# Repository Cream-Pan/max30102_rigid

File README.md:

<div id="top"></div>

# MAX30102_rigid

MAX30102を用いた小型PPGセンサ用リジッド基板である．
耳装着型デバイスやウェアラブルデバイスへの組み込みを想定し，光電脈波（PPG）を取得するために設計した．

## 使用技術一覧

## 目次

1. [概要](#概要)
2. [基板仕様](#基板仕様)
3. [回路構成](#回路構成)
4. [ディレクトリ構成](#ディレクトリ構成)
5. [Git管理方針](#git管理方針)
6. [製造データ](#製造データ)
7. [設計上の注意](#設計上の注意)

## 概要

本リポジトリは，MAX30102を搭載したリジッド基板のKiCadプロジェクトを管理するためのものである．
MAX30102は，赤色LED，赤外LED，フォトダイオード，ADCを内蔵した光学式センサであり，PPG波形の取得や心拍推定に利用できる．

本基板では，MAX30102を小型基板上に実装し，外部マイコンからI2C経由でPPGデータを取得する構成としている．

<p align="right">(<a href="#top">トップへ</a>)</p>

---

## 基板仕様

| 項目      | 内容                     |
| ------- | ---------------------- |
| 基板名     | MAX30102_rigid         |
| センサ     | MAX30102               |
| 通信方式    | I2C                    |
| I2Cアドレス | 0x57                   |
| 取得データ   | Red / IR PPG           |
| 用途      | PPG取得，心拍推定，ウェアラブルセンシング |
| 設計ツール   | KiCad                  |

<p align="right">(<a href="#top">トップへ</a>)</p>

---

## 回路構成

本基板は，MAX30102と外部マイコンをI2Cで接続する構成である．

```text
MCU
├── SDA
├── SCL
└── INT

MAX30102
├── Red LED
├── IR LED
├── Photodiode
├── ADC
└── FIFO
```

MAX30102内部のFIFOに格納されたPPGデータをマイコン側で読み出し，心拍推定や波形解析に利用する．

<p align="right">(<a href="#top">トップへ</a>)</p>

---

## ディレクトリ構成

```text
.
├── .gitignore
├── .history/                         # VSCode等の履歴フォルダ，Git管理対象外
├── garbar/                           # Gerber出力用フォルダ
├── jlcpcb/                           # JLCPCB発注用データ
├── MAX30102_rigid-backups/           # KiCadバックアップ，Git管理対象外
├── fp-info-cache                     # KiCadキャッシュ，Git管理対象外
├── MAX30102_rigid.kicad_pcb          # PCBレイアウト
├── MAX30102_rigid.kicad_prl          # KiCadローカル設定，Git管理対象外
├── MAX30102_rigid.kicad_pro          # KiCadプロジェクト
├── MAX30102_rigid.kicad_sch          # 回路図
└── MAX30102_test1.kicad_prl          # KiCadローカル設定，Git管理対象外
```

基本的に，Gitで管理する主要ファイルは以下である．

```text
MAX30102_rigid.kicad_pro
MAX30102_rigid.kicad_sch
MAX30102_rigid.kicad_pcb
.gitignore
README.md
```

<p align="right">(<a href="#top">トップへ</a>)</p>

---

## Git管理方針

本リポジトリでは，KiCadプロジェクト本体をGitで管理し，自動生成ファイルや個人環境依存ファイルは管理対象外とする．

主に以下をGit管理対象外とする．

```text
*.kicad_prl
fp-info-cache
*-backups/
*_backups/
*.bak
*-bak
_autosave-*
*.lck
.history/
```

また，製造出力ファイルも基本的には自動生成物として扱う．

```text
*.gbr
*.drl
*.pos
*.rpt
*.zip
```

本プロジェクトでは，自作シンボルおよび自作フットプリントを `kicad_my_library` リポジトリで管理している．  
KiCadで本プロジェクトを開く前に，`kicad_my_library` をcloneし，KiCadのライブラリ設定に登録する必要がある．

```powershell
git clone https://github.com/Cream-Pan/kicad_my_library.git
```

登録するライブラリは以下である．

```text
Footprint Library:
kicad_my_library/footprints/MyLibrary.pretty

Symbol Library:
kicad_my_library/symbols/MyLibrary.kicad_sym
```

KiCad上でのライブラリNicknameは以下に統一する．
```text
MyLibrary
```

Nicknameを変更すると，MyLibrary:C0603 のような既存の参照が壊れる可能性がある．

発注時点の製造データを残す場合は，必要に応じてGitHub Releasesや別フォルダで管理する．

<p align="right">(<a href="#top">トップへ</a>)</p>

---

## 製造データ

`jlcpcb` フォルダには，JLCPCBでの基板製造および部品実装を想定したデータを配置する．

主な出力対象は以下である．

* Gerber
* Drill
* BOM
* CPL

現状の `.gitignore` では，`.gbr`，`.drl`，`.zip` などの製造出力はGit管理対象外としている．
そのため，発注データをGitHub上に残したい場合は，`.gitignore` の例外設定またはGitHub Releasesでの管理を検討する．

<p align="right">(<a href="#top">トップへ</a>)</p>

---

## 設計上の注意

### 1．電源

MAX30102では，LED駆動時にパルス的な電流が流れるため，電源ラインの安定性が重要である．
VLEDおよびVDD近傍にデカップリングコンデンサを配置し，電源ノイズがPPG信号に混入しにくい構成とする．

### 2．光学設計

PPG信号は，センサと皮膚の距離，接触状態，外光の混入に影響される．
そのため，実装時には以下に注意する．

* センサと皮膚の距離を一定に保つ
* 外光を遮断する
* 光学窓上にフラックス残渣や汚れを残さない
* 皮膚との接触圧が過度に変動しない構造にする

### 3．I2C通信

MAX30102はI2Cで通信するため，SDAおよびSCLのプルアップ抵抗，配線長，ノイズ混入に注意する．
複数センサと同一バス上で使用する場合は，I2Cアドレスの重複やバス容量にも注意する．

<p align="right">(<a href="#top">トップへ</a>)</p>

---

開発者情報
Name: Takato Ishii

Portfolio: https://takato-ishii.vercel.app/

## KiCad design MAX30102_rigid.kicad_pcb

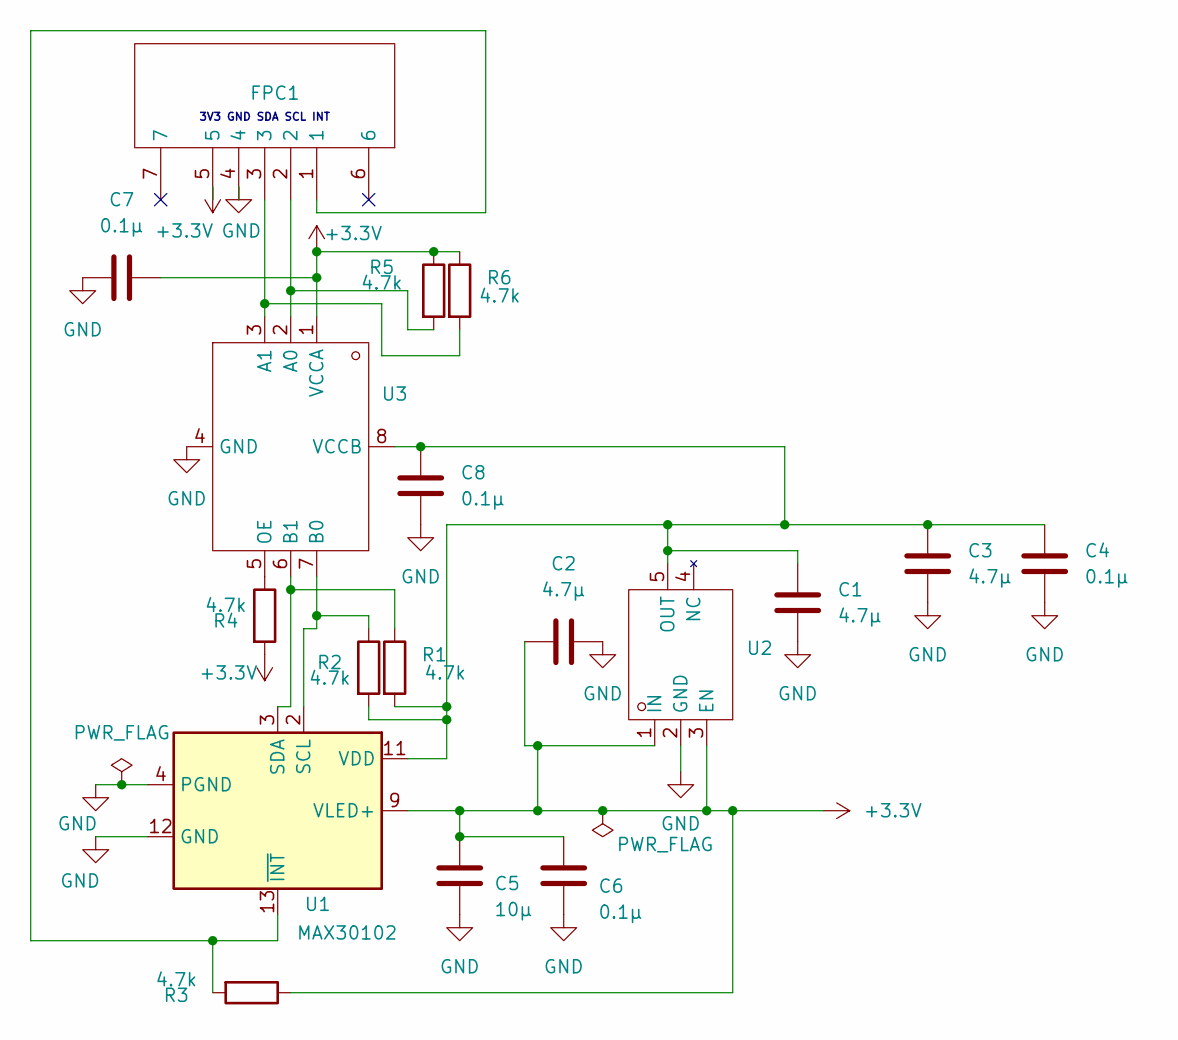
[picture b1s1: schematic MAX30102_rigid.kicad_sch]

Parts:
C1, C2, C3: 4.7μ; C0603
C4, C6, C7, C8: 0.1μ; C_0402_1005Metric
C5: 10μ; C0603
FPC1: FPC-SMD_AFC07-S05FCC-00; Manufacturer Part AFC07-S05FCC-00; LCSC Part Name 间距:0.5mm P数:5P 抽屉式 下接
R1, R2, R3, R4, R5, R6: 4.7k; R_0402_1005Metric
U1: MAX30102; Maxim_OLGA-14_3.3x5.6mm_P0.8mm
U2: SOT-23-5_L2.9-W1.6-P0.95-LS2.8-BL; Manufacturer Part TPS7A0218PDBVR; LCSC Part Name 具有使能功能的 200mA、毫微功耗 IQ (25nA)、低压降 (LDO) 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
U3: MICROPARK_L1.6-W1.6-P0.50-BL-1; Manufacturer Part FXMA2102L8X; LCSC Part Name 双电源 2位电压转换器/缓冲器/中继器/隔离器 用于I2C应用

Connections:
+3.3V: C2.1, C5.1, C6.1, C7.1, FPC1.5, R3.1, R4.2, R5.1, R6.1, U1.9 (VLED+), U1.10 (VLED+), U2.1 (IN), U2.3 (EN), U3.1 (VCCA)
GND: C1.2, C2.2, C3.2, C4.2, C5.2, C6.2, C7.2, C8.2, FPC1.4, U1.4 (PGND), U1.12 (GND), U2.2 (GND), U3.4 (GND)
unnamed: R2.1, U1.2 (SCL), U3.7 (B0)
unnamed: R1.1, U1.3 (SDA), U3.6 (B1)
unnamed: C1.1, C3.1, C4.1, C8.1, R1.2, R2.2, U1.11 (VDD), U2.5 (OUT), U3.8 (VCCB)
unnamed: FPC1.1, R3.2, U1.13 (~INT)
unnamed: FPC1.2, R5.2, U3.2 (A0)
unnamed: FPC1.3, R6.2, U3.3 (A1)
unnamed: R4.1, U3.5 (OE)

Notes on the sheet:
3V3 GND SDA SCL INT

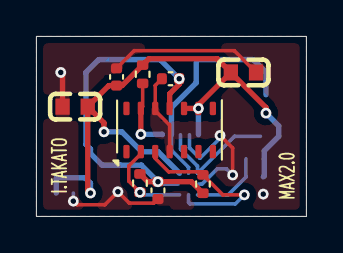
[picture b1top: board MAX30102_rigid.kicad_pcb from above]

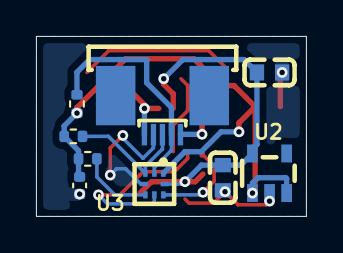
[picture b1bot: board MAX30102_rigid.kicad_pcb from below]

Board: 2 copper layers, 15.0 x 10.0 mm, 18 parts (9 on the bottom side), 9 nets.

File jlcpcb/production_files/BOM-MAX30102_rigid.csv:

Comment,Designator,Footprint,LCSC,Quantity
0.1μ,"C4,C6,C7,C8",C_0402_1005Metric,C77020,4
10μ,C5,C0603,C2959727,1
4.7k,"R1,R2,R3,R4,R5,R6",R_0402_1005Metric,C281778,6
4.7μ,"C1,C2,C3",C0603,C389010,3
MAX30102,U1,Maxim_OLGA-14_3.3x5.6mm_P0.8mm,C6454833,1
~,U3,MICROPARK_L1.6-W1.6-P0.50-BL-1,C107408,1
~,FPC1,FPC-SMD_AFC07-S05FCC-00,C262199,1
~,U2,SOT-23-5_L2.9-W1.6-P0.95-LS2.8-BL,C3748843,1

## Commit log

2026-06-01 Initial KiCad project
2026-06-01 Add README
2026-06-04 Update for Order
